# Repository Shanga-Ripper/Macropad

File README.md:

# Macropad
This is my Macropad.

BOM for my Macropad:
1. 4x Cherry MX Switches:
  Link : https://www.alibaba.com/product-detail/Cherry-mechanical-Keyboard-key-touch-Micro_1601204407658.html?spm=a2700.prosearch.normal_offer.d_image.183267afHfnEJ0&priceId=53afa7db8cfd46a7952ed8fc7a63f760, Manufacturer : Alibaba,
  Total Cost : $0.41
2. 2x DSA Keycaps:
   Link: https://www.alibaba.com/suppliersubdomainalibabacom/product-detail/PBT-Colorful-Keycaps-for-Mechanical-Keyboard_1601712196348.html?spm=a2700.prosearch.normal_offer.d_image.44c667afrCAsDR&priceId=46677dda65da4e8da5d13f48e3ea3673,  Manufacturer : Alibaba, 
   Total Cost : $1.63
4. 10x SK6812MINI-E RGB LEDs:
   Link : https://www.alibaba.com/product-detail/Reverse-Mount-6028-Rgb-Smd-Led_1600640673301.html?spm=a2700.prosearch.normal_offer.d_image.6e3b67afbiULBB&priceId=30f23cf973d64fbda3495a9ca82fa3ee,  Manufacturer : Alibaba, 
   Total Cost : $0.45
6. 1x 0.91" 128x32 OLED Display:
  Link : https://www.alibaba.com/product-detail/0-91-Inch-OLED-Display-Screen_1601418193533.html?spm=a2700.prosearch.normal_offer.d_image.5a2967afCjDuO1&priceId=cd9784d7f7734851b92d56c7dc479605,  Manufacturer : Alibaba, 
  Total Cost : $0.88
8. 2x EC11 Rotary Encoder:
  Link : https://www.alibaba.com/product-detail/20mm-Audio-Digital-Potentiometer-Rotary-Encoder_1601112137034.html?spm=a2700.prosearch.normal_offer.d_image.339f67af0KrhYF&priceId=165095eda4674ee99a13386a2b30070a,  Manufacturer : Alibaba, 
  Total Cost : $0.59
9. 1x XIAO RP2040:
  Link : https://www.alibaba.com/product-detail/For-Nano-RP2040-Motherboard-Seeed-Studio_1601721854998.html?spm=a2700.prosearch.normal_offer.d_image.67ba67af5q1QJt&priceId=cce3d74f47614445b6886fc1c0f89cc1,  Manufacturer : Alibaba, 
  Total Cost : $3.81 
10. 1x Case (2x 3d printed parts)
  Friend, 
  No Cost

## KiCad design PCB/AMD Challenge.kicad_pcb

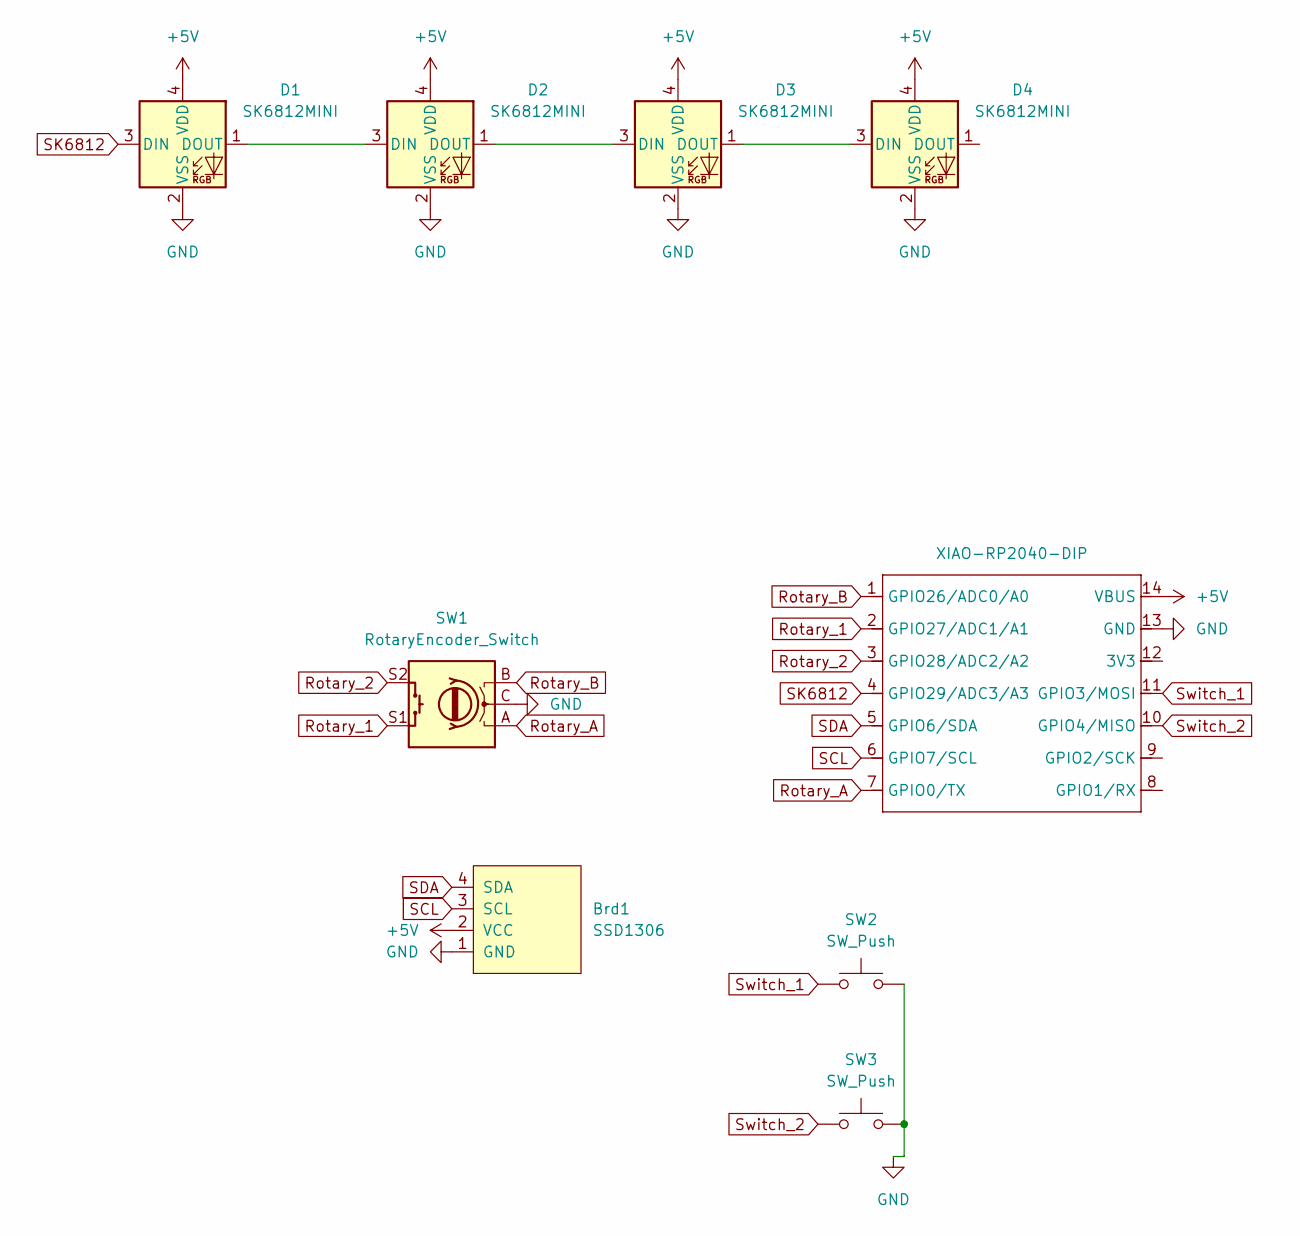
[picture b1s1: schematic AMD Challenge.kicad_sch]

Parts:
Brd1: SSD1306; SSD1306-0.91-OLED-4pin-128x32
D1, D2, D3, D4: SK6812MINI; SK6812MINI-E_fixed
SW1: RotaryEncoder_Switch; RotaryEncoder_Alps_EC11E-Switch_Vertical_H20mm
SW2, SW3: SW_Push; SW_Cherry_MX_1.00u_PCB
U1: XIAO-RP2040-DIP

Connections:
+5V: Brd1.2 (VCC), D1.4 (VDD), D2.4 (VDD), D3.4 (VDD), D4.4 (VDD), U1.14 (VBUS)
GND: Brd1.1 (GND), D1.2 (VSS), D2.2 (VSS), D3.2 (VSS), D4.2 (VSS), SW1.C, SW2.2, SW3.2, U1.13 (GND)
unnamed: D1.1 (DOUT), D2.3 (DIN)
unnamed: D2.1 (DOUT), D3.3 (DIN)
unnamed: D3.1 (DOUT), D4.3 (DIN)
Rotary_1: SW1.S1, U1.2 (GPIO27/ADC1/A1)
Rotary_2: SW1.S2, U1.3 (GPIO28/ADC2/A2)
Rotary_A: SW1.A, U1.7 (GPIO0/TX)
Rotary_B: SW1.B, U1.1 (GPIO26/ADC0/A0)
SCL: Brd1.3 (SCL), U1.6 (GPIO7/SCL)
SDA: Brd1.4 (SDA), U1.5 (GPIO6/SDA)
SK6812: D1.3 (DIN), U1.4 (GPIO29/ADC3/A3)
Switch_1: SW2.1, U1.11 (GPIO3/MOSI)
Switch_2: SW3.1, U1.10 (GPIO4/MISO)

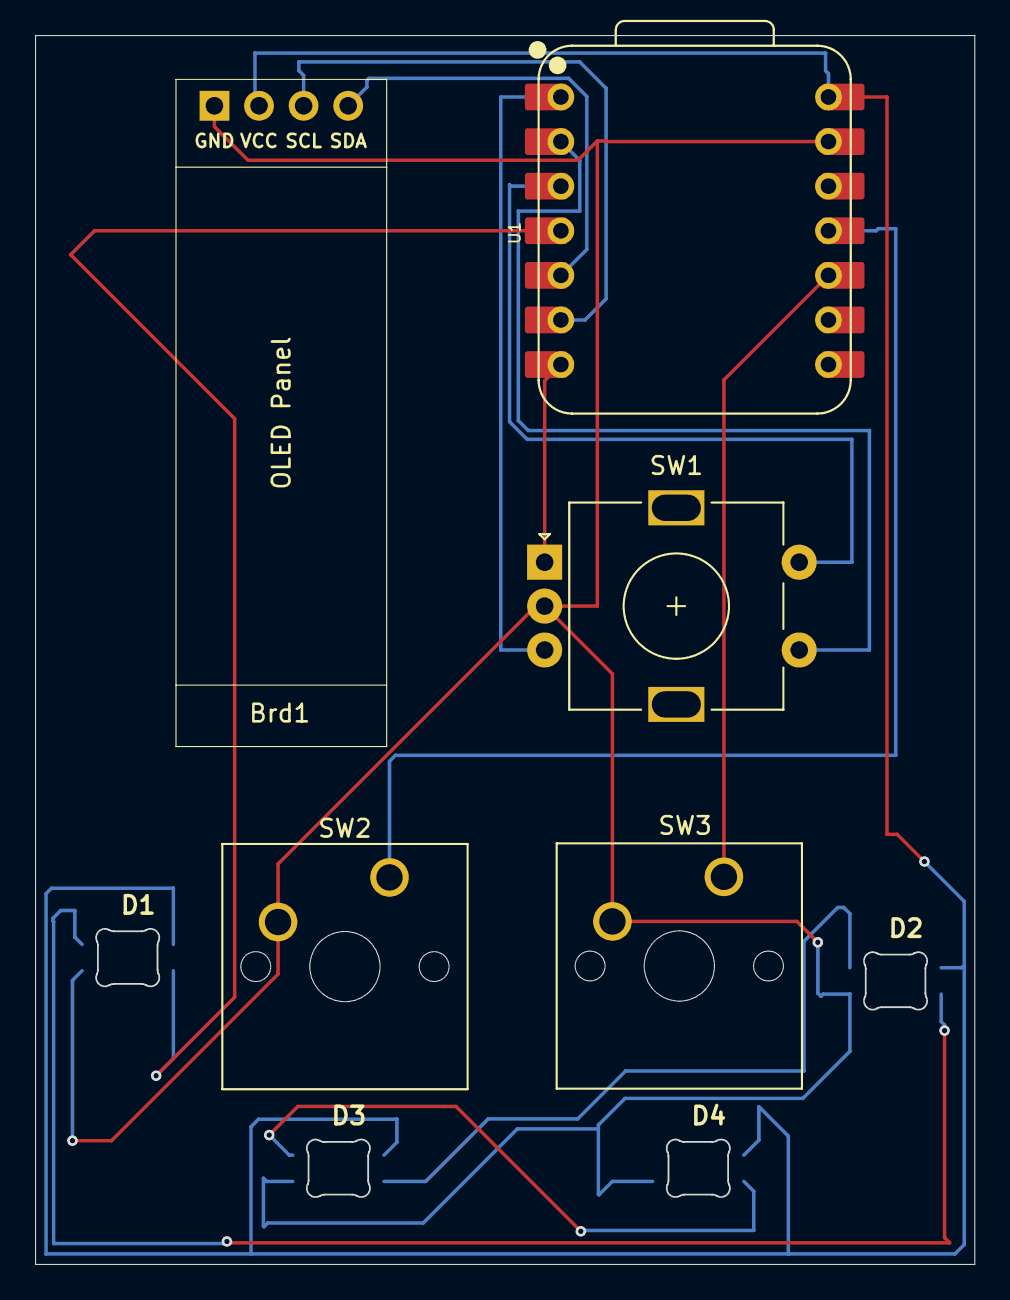
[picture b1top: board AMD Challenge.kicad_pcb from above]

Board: 2 copper layers, 53.5 x 70.0 mm, 9 parts (0 on the bottom side), 14 nets.

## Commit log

2026-03-29 Create dontreadme
2026-03-29 Create Default
2026-03-29 Create Keymap
2026-03-31 Create Dont
